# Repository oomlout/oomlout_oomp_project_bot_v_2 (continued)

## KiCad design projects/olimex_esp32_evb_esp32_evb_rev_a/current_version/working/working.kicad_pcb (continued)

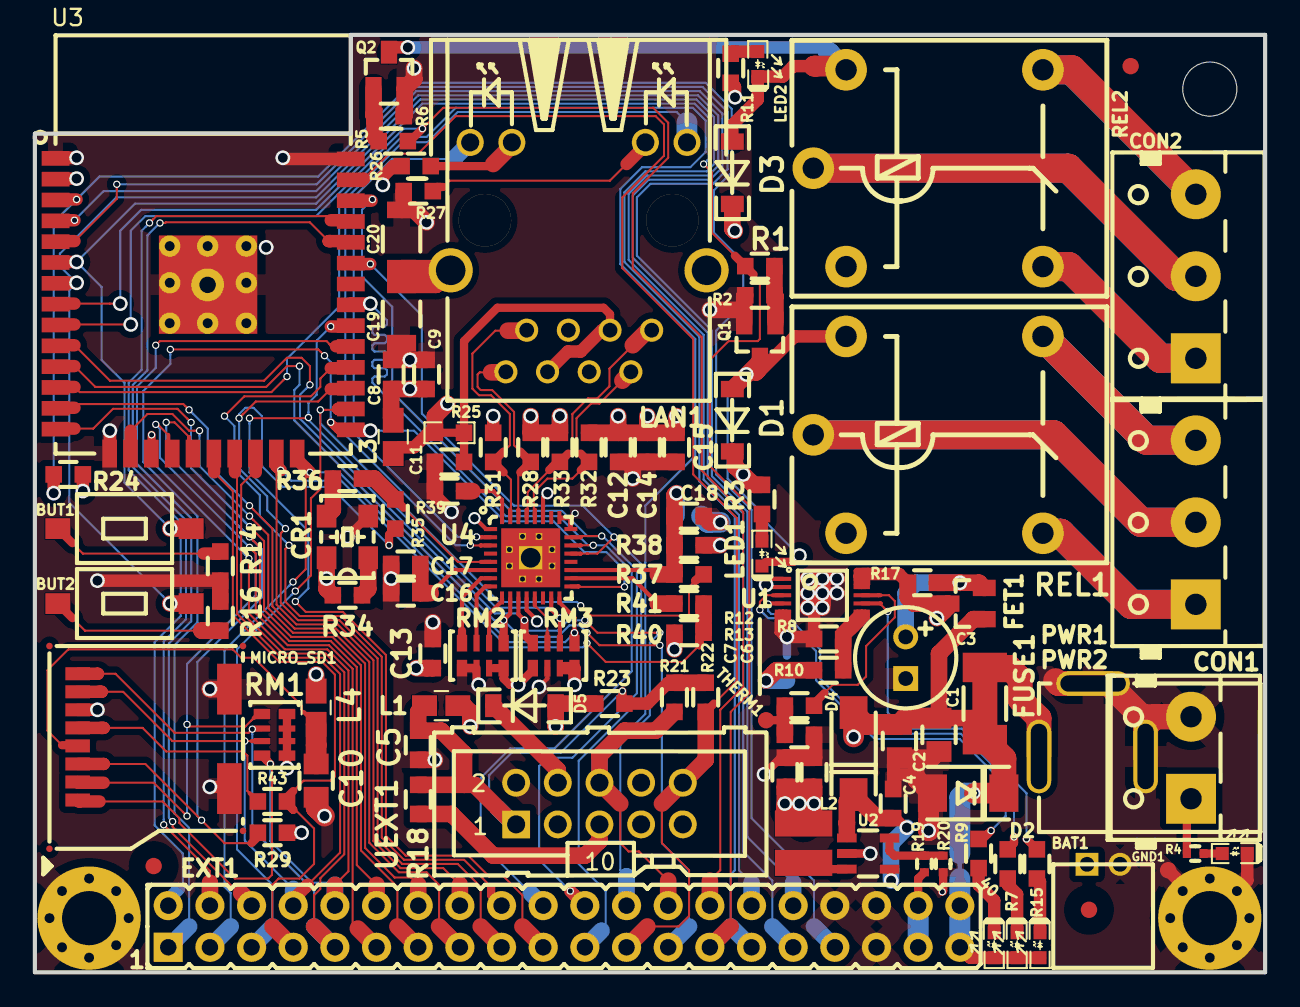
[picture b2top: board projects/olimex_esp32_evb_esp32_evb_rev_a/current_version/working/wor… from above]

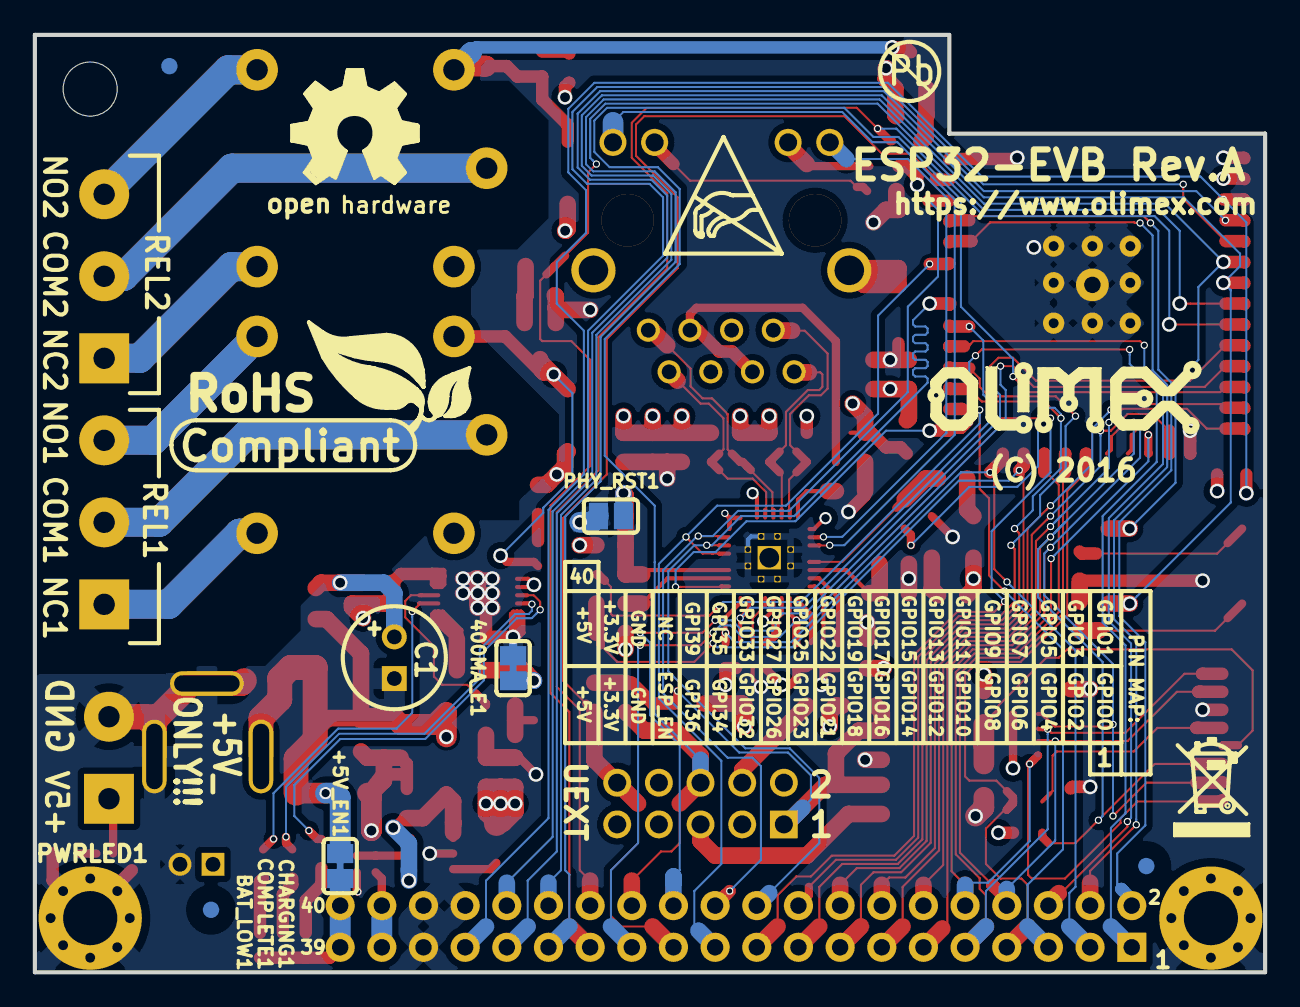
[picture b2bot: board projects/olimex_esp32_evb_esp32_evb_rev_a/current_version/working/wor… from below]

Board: 4 copper layers, 75.0 x 57.2 mm, 111 parts (5 on the bottom side), 91 nets.

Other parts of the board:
MH1: Mounting_hole_Shield_3.3mm; Mounting_hole_3.3mm
Ref**: Val**; LOGO_ANTISTATIC_1
Ref**#2: Val**; LOGO_ROHS_1
